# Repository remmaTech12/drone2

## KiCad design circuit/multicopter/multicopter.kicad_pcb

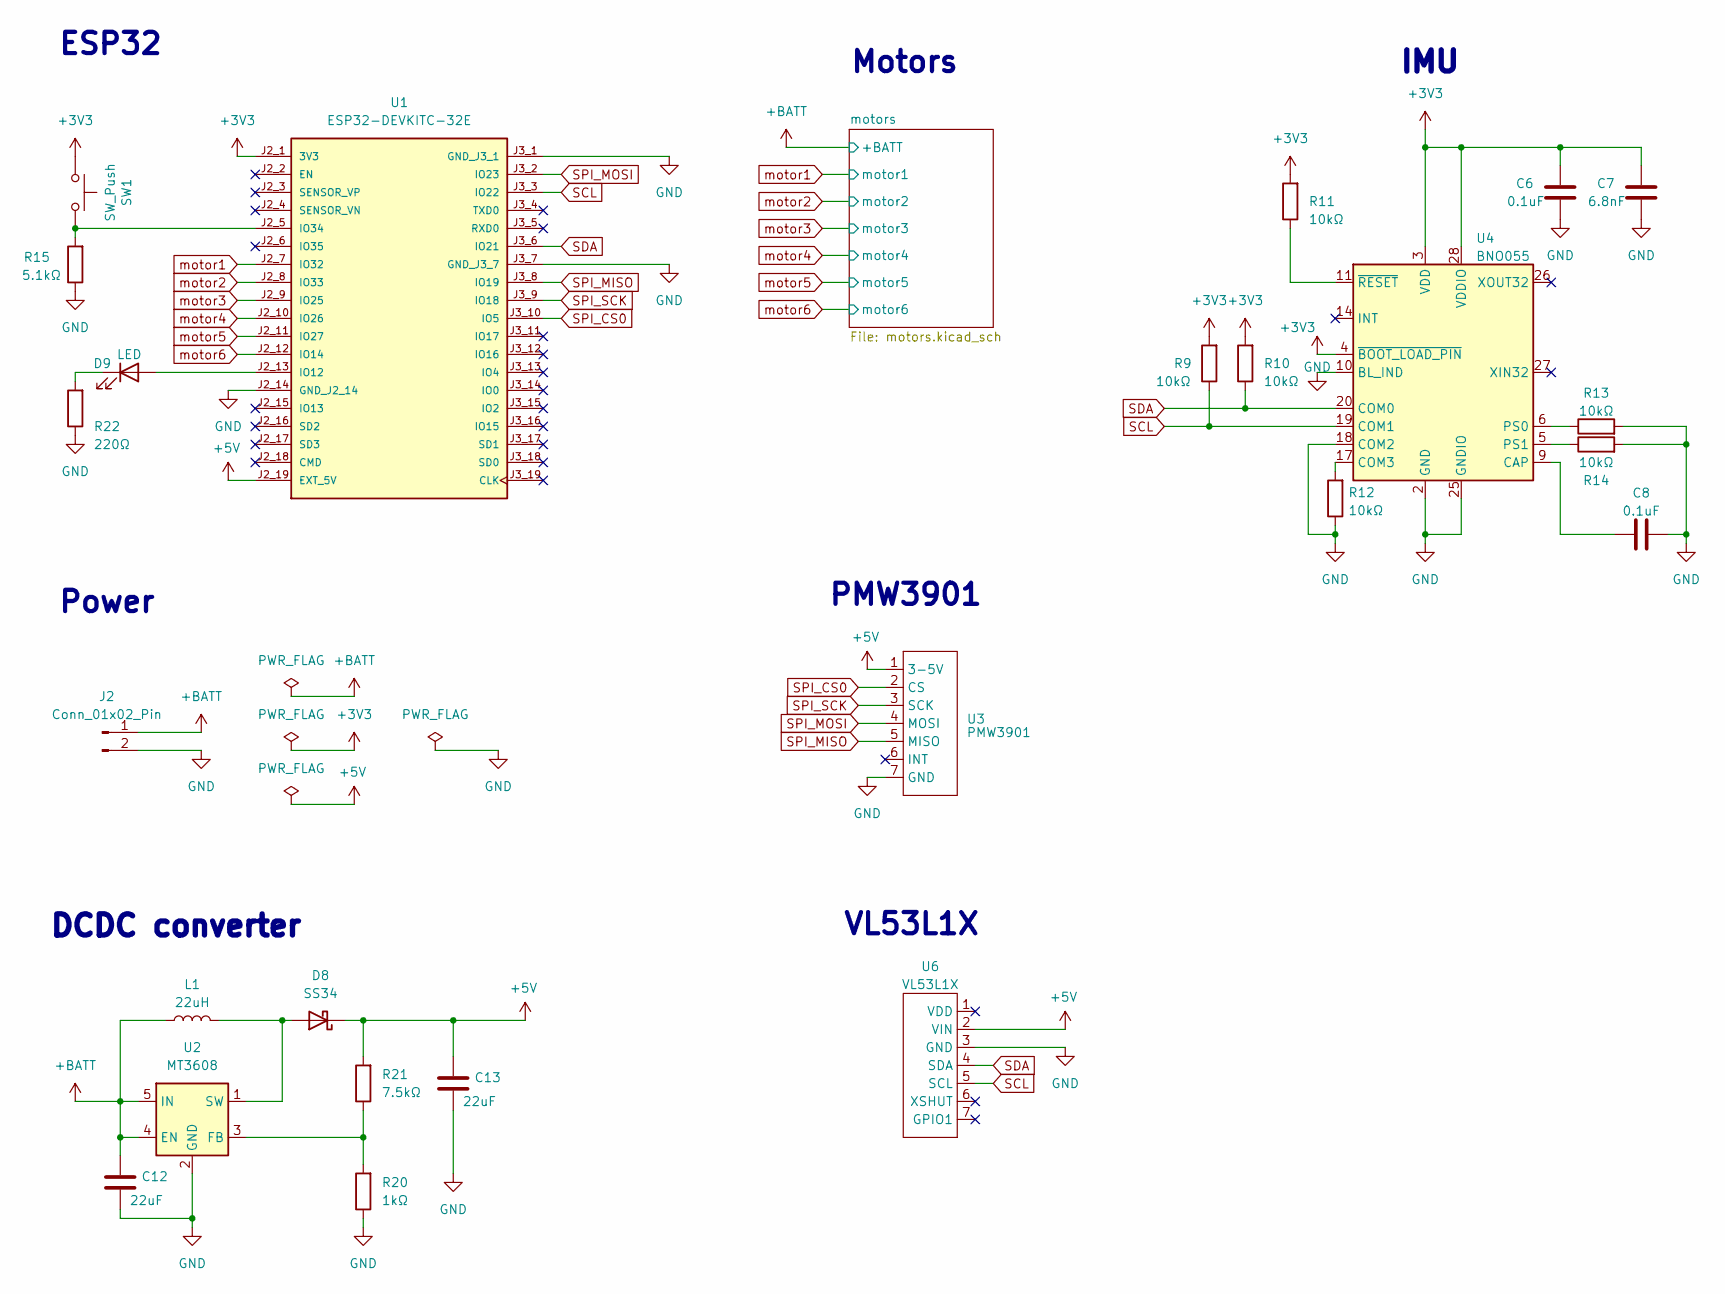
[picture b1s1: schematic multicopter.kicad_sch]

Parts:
C6, C8: 0.1uF; C_0603_1608Metric
C7: 6.8nF; C_0603_1608Metric
C12, C13: 22uF; C_0603_1608Metric
D8: SS34; D_SOD-123F
D9: LED; D_0603_1608Metric
J2: Conn_01x02_Pin; PinHeader_1x02_P2.54mm_Vertical
L1: 22uH; L_Vishay_IHLP-2020
R9, R10, R11, R12, R13, R14: 10kΩ; R_0603_1608Metric
R15: 5.1kΩ; R_0603_1608Metric
R20: 1kΩ; R_0603_1608Metric
R21: 7.5kΩ; R_0603_1608Metric
R22: 220Ω; R_0603_1608Metric
SW1: SW_Push; SW_Push_1P1T_NO_CK_KMR2
U1: ESP32-DEVKITC-32E; MODULE_ESP32-DEVKITC-32E; PARTREV 1.4
U2: MT3608; SOT-23-6
U3: PMW3901; JST_PH_B7B-PH-K_1x07_P2.00mm_Vertical
U4: BNO055; LGA-28_5.2x3.8mm_P0.5mm
U6: VL53L1X; JST_PH_B7B-PH-K_1x07_P2.00mm_Vertical

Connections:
+3V3: C6.2, C7.2, R9.2, R10.2, R11.2, SW1.1, U1.J2_1 (3V3), U4.3 (VDD), U4.4 (~BOOT_LOAD_PIN), U4.28 (VDDIO)
+5V: C13.1, D8.1 (K), R21.2, U1.J2_19 (EXT_5V), U3.1 (3-5V), U6.2 (VIN)
+BATT: C12.1, J2.1, L1.1, U2.4 (EN), U2.5 (IN); also elsewhere on the board
GND: C6.1, C7.1, C8.2, C12.2, C13.2, J2.2, R12.1, R13.2, R14.2, R15.1, R20.1, R22.1, U1.J2_14 (GND_J2_14), U1.J3_1 (GND_J3_1), U1.J3_7 (GND_J3_7), U2.2 (GND), U3.7 (GND), U4.2 (GND), U4.10 (BL_IND), U4.18 (COM2), U4.25 (GNDIO), U6.3 (GND); also elsewhere on the board
unnamed: D8.2 (A), L1.2, U2.1 (SW)
unnamed: D9.2 (A), U1.J2_13 (IO12)
unnamed: D9.1 (K), R22.2
unnamed: R15.2, SW1.2, U1.J2_5 (IO34)
unnamed: R20.2, R21.1, U2.3 (FB)
unnamed: C8.1, U4.9 (CAP)
unnamed: R12.2, U4.17 (COM3)
unnamed: R13.1, U4.6 (PS0)
unnamed: R14.1, U4.5 (PS1)
unnamed: R11.1, U4.11 (~RESET)
SCL: R9.1, U1.J3_3 (IO22), U4.19 (COM1), U6.5 (SCL)
SDA: R10.1, U1.J3_6 (IO21), U4.20 (COM0), U6.4 (SDA)
SPI_CS0: U1.J3_10 (IO5), U3.2 (CS)
SPI_MISO: U1.J3_8 (IO19), U3.5 (MISO)
SPI_MOSI: U1.J3_2 (IO23), U3.4 (MOSI)
SPI_SCK: U1.J3_9 (IO18), U3.3 (SCK)
motor1: U1.J2_7 (IO32); also elsewhere on the board
motor2: U1.J2_8 (IO33); also elsewhere on the board
motor3: U1.J2_9 (IO25); also elsewhere on the board
motor4: U1.J2_10 (IO26); also elsewhere on the board
motor5: U1.J2_11 (IO27); also elsewhere on the board
motor6: U1.J2_12 (IO14); also elsewhere on the board

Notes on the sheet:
Motors
VL53L1X
DCDC converter
PMW3901
Power
ESP32
IMU

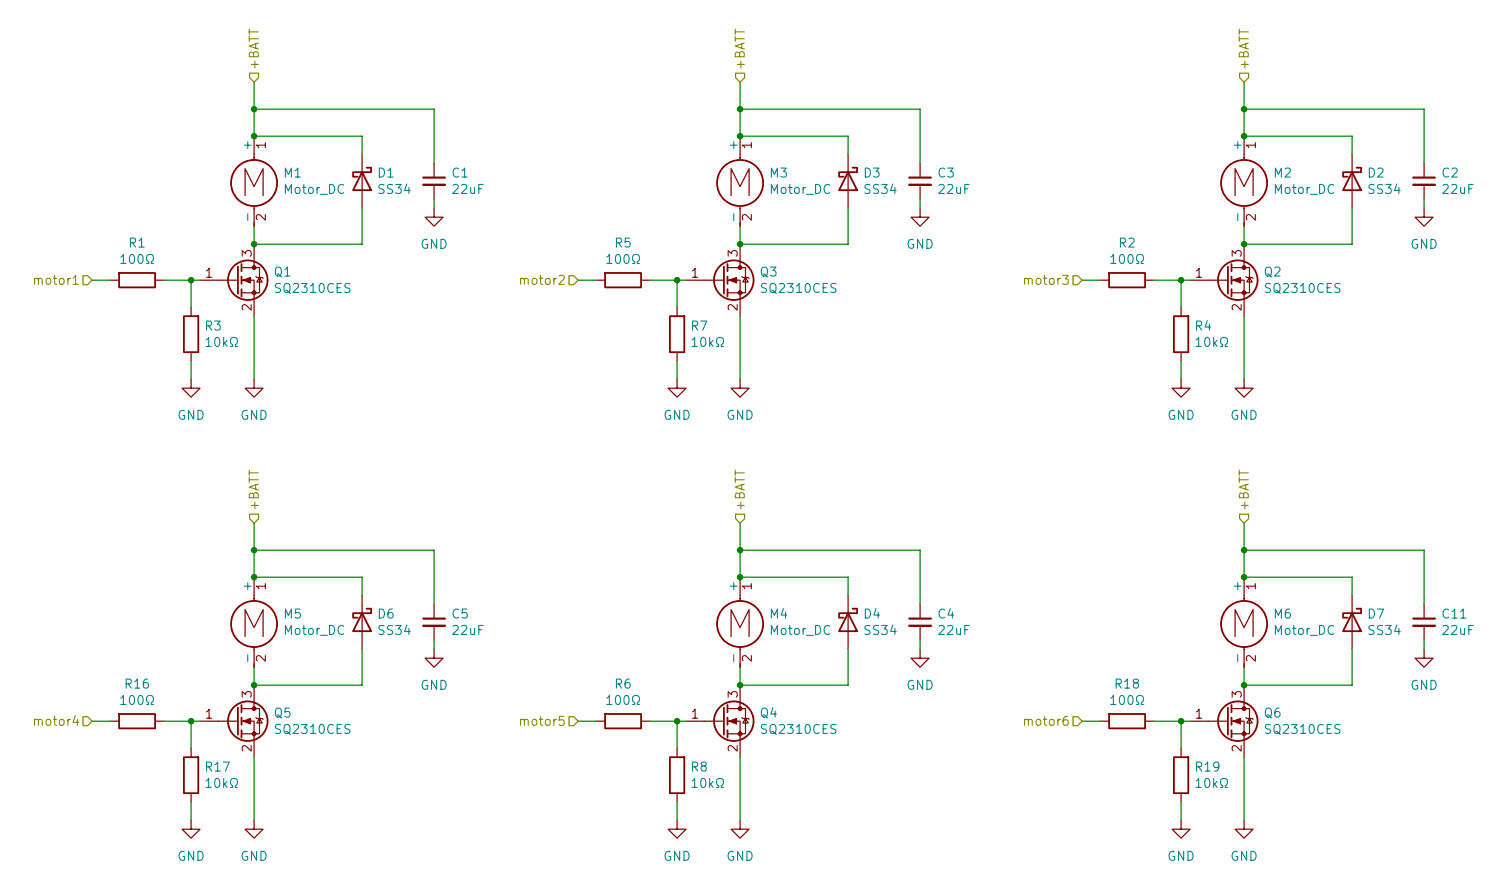
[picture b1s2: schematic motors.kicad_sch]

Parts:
C1, C2, C3, C4, C5, C11: 22uF; C_1206_3216Metric
D1, D2, D3, D4, D6, D7: SS34; D_SMC
M1, M2, M3, M4, M5, M6: Motor_DC; PinHeader_1x02_P2.54mm_Vertical
Q1, Q2, Q3, Q4, Q5, Q6: SQ2310CES; SOT-23
R1, R2, R5, R6, R16, R18: 100Ω; R_1210_3225Metric
R3, R4, R7, R8, R17, R19: 10kΩ; R_0201_0603Metric

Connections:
+BATT: C1.1, C2.1, C3.1, C4.1, C5.1, C11.1, D1.1 (K), D2.1 (K), D3.1 (K), D4.1 (K), D6.1 (K), D7.1 (K), M1.1 (+), M2.1 (+), M3.1 (+), M4.1 (+), M5.1 (+), M6.1 (+); also elsewhere on the board
GND: C1.2, C2.2, C3.2, C4.2, C5.2, C11.2, Q1.2 (S), Q2.2 (S), Q3.2 (S), Q4.2 (S), Q5.2 (S), Q6.2 (S), R3.1, R4.1, R7.1, R8.1, R17.1, R19.1; also elsewhere on the board
unnamed: D1.2 (A), M1.2 (-), Q1.3 (D)
unnamed: D2.2 (A), M2.2 (-), Q2.3 (D)
unnamed: D3.2 (A), M3.2 (-), Q3.3 (D)
unnamed: D4.2 (A), M4.2 (-), Q4.3 (D)
unnamed: D6.2 (A), M5.2 (-), Q5.3 (D)
unnamed: D7.2 (A), M6.2 (-), Q6.3 (D)
unnamed: Q1.1 (G), R1.1, R3.2
unnamed: Q2.1 (G), R2.1, R4.2
unnamed: Q3.1 (G), R5.1, R7.2
unnamed: Q4.1 (G), R6.1, R8.2
unnamed: Q5.1 (G), R16.1, R17.2
unnamed: Q6.1 (G), R18.1, R19.2
motor1: R1.2; also elsewhere on the board
motor2: R5.2; also elsewhere on the board
motor3: R2.2; also elsewhere on the board
motor4: R16.2; also elsewhere on the board
motor5: R6.2; also elsewhere on the board
motor6: R18.2; also elsewhere on the board

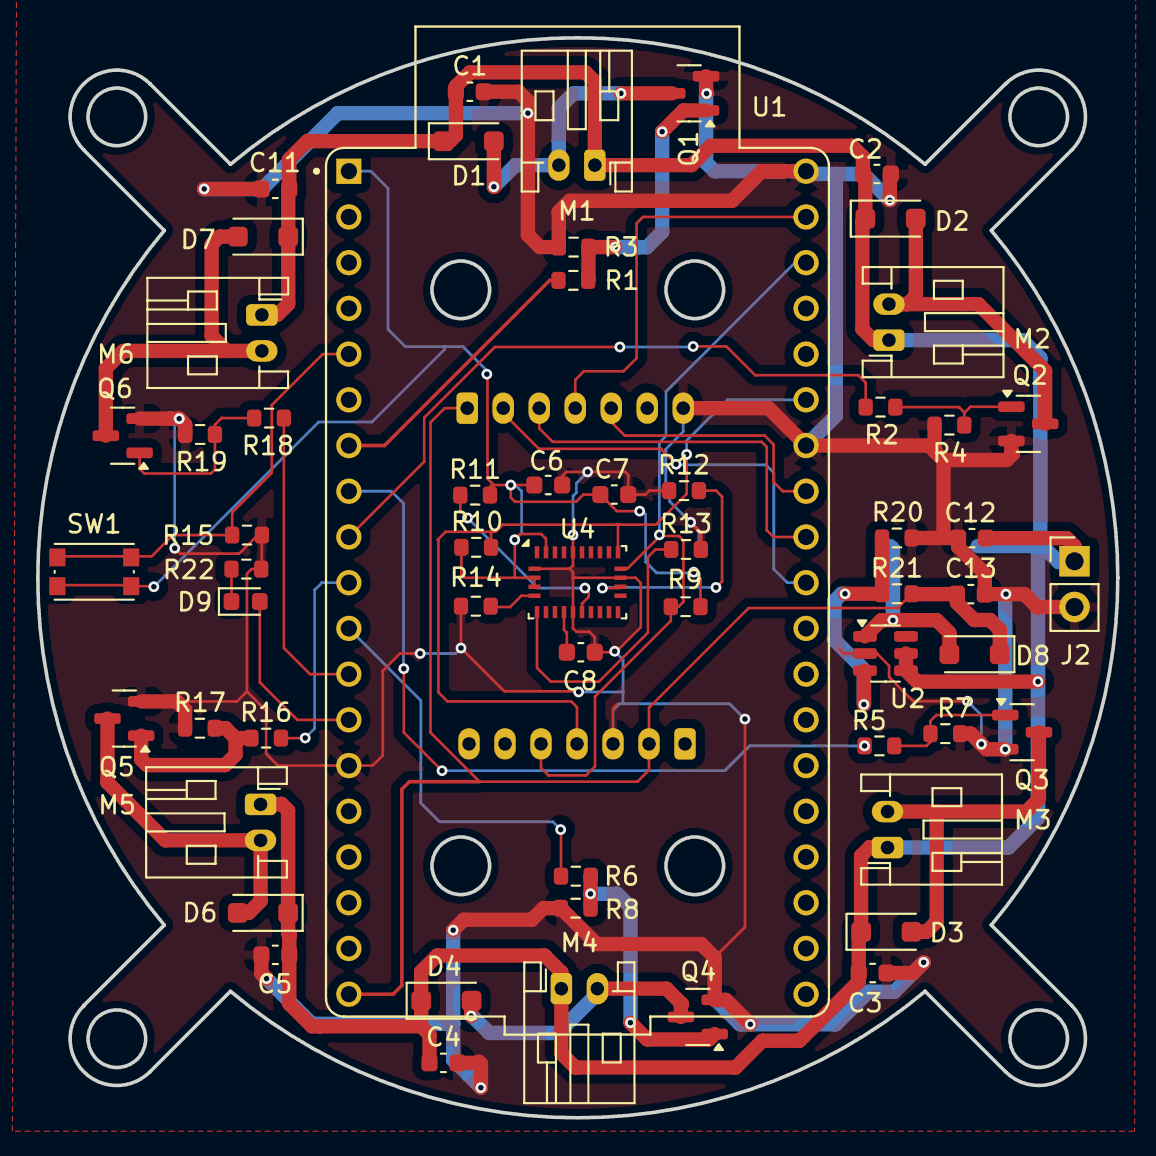
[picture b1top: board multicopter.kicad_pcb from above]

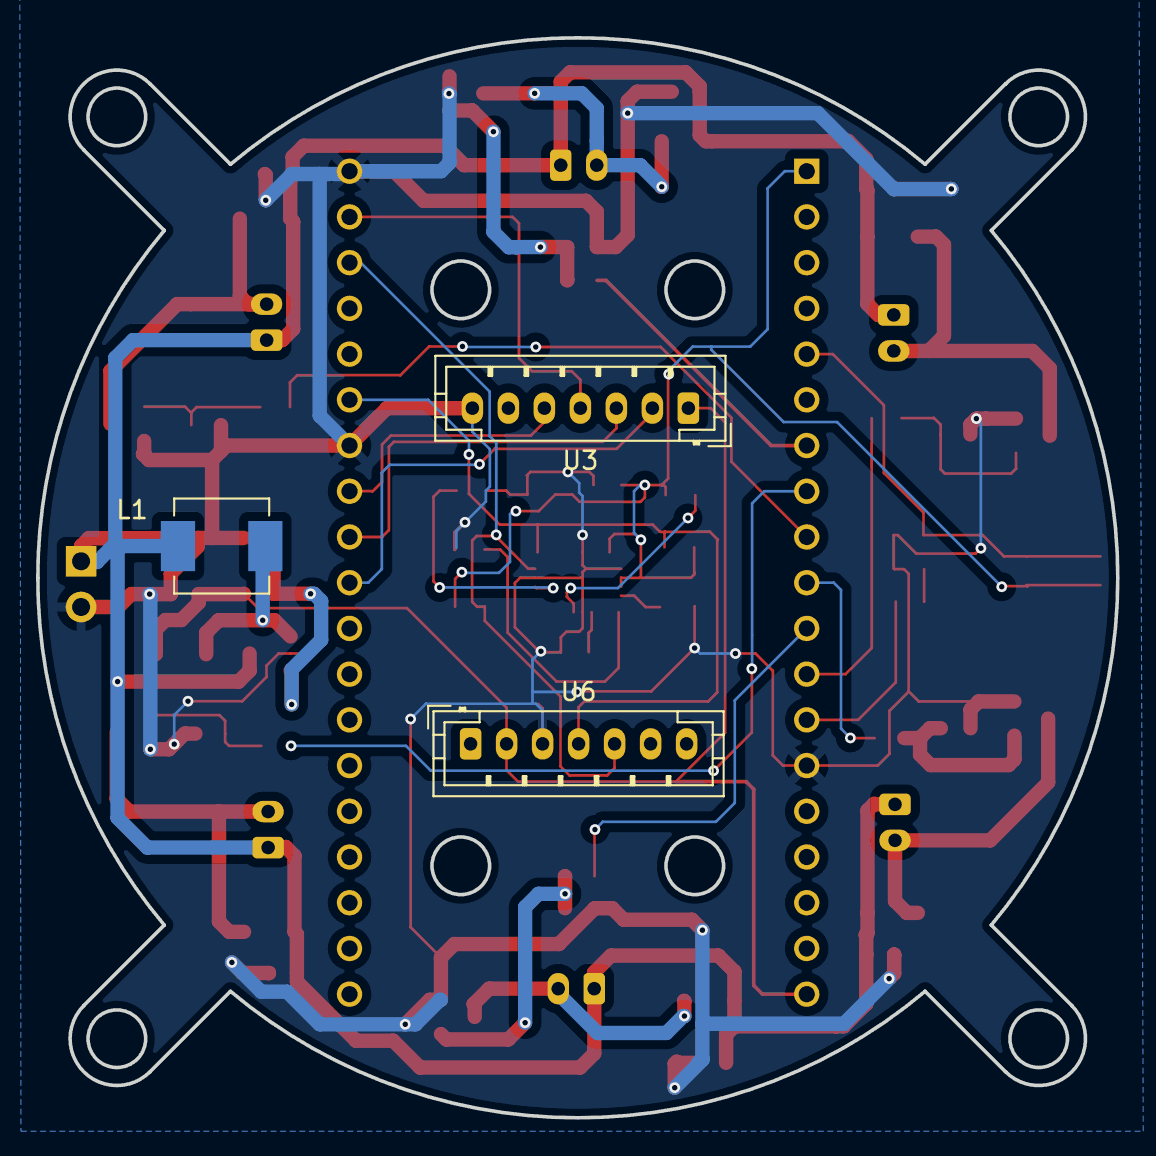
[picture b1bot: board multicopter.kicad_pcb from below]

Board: 2 copper layers, 60.0 x 60.0 mm, 61 parts (3 on the bottom side), 38 nets.

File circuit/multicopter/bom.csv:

"Designator","Description/Value","Package/Footprint","Quantity","Manufacturer","Purchase Link","Production Number","Mounting Type","Unit Price"
"J2","Conn_01x02_Pin","Connector_PinHeader_2.54mm:PinHeader_1x02_P2.54mm_Vertical","1","","","","THT",""
"U1","ESP32-DEVKITC-32E","ESP32-DEVKITC-32E:MODULE_ESP32-DEVKITC-32E","1","CXH","https://www.alibaba.com/product-detail/2-54mm-Pitch-1x19-pin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","","THT","74.66"
"R15","5.1kΩ","Resistor_SMD:R_0603_1608Metric","1","Vishay / Dale ","https://www.mouser.jp/ProductDetail/Vishay-Dale/CRCW06035K10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"," CRCW06035K10FKEC ","SMD","19.8"
"R20","1kΩ","Resistor_SMD:R_0603_1608Metric","1"," TDK ","https://www.mouser.jp/ProductDetail/TDK/MMZ1608S102ATA00?qs=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"," MMZ1608S102ATA00 ","SMD","16.5"
"M1,M2,M3,M4,M5,M6","Motor_DC","Connector_JST:JST_PH_S2B-PH-K_1x02_P2.00mm_Horizontal","6","JST Sales America Inc.","https://www.digikey.jp/en/products/detail/jst-sales-america-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"," S2B-PH-K-S","THT","15.04"
"C7","6.8nF","Capacitor_SMD:C_0603_1608Metric","1","Vishay / Vitramon ","https://www.mouser.jp/ProductDetail/Vishay-Vitramon/VJ0603Y6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"," VJ0603Y682KXBAC31X ","SMD","41.3"
"C1,C2,C3,C4,C5,C11,C12,C13","22uF","Capacitor_SMD:C_0603_1608Metric","8","KYOCERA AVX ","https://www.mouser.jp/ProductDetail/KYOCERA-AVX/0603ZD226MAT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","0603ZD226MAT2A ","SMD","85.8"
"U3","PMW3901","Connector_JST:JST_PH_B7B-PH-K_1x07_P2.00mm_Vertical","1","JST Sales America Inc.","https://www.digikey.jp/ja/products/detail/jst-sales-america-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","B7B-PH-K-S","THT","50.77"
"U6","VL53L1X","Connector_JST:JST_PH_B7B-PH-K_1x07_P2.00mm_Vertical","1","JST Sales America Inc.","https://www.digikey.jp/ja/products/detail/jst-sales-america-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","B7B-PH-K-S","THT","50.77"
"U4","BNO055","Package_LGA:LGA-28_5.2x3.8mm_P0.5mm","1","Bosch Sensortec","https://www.mouser.jp/ProductDetail/Bosch-Sensortec/BNO055?q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","BNO055","SMD","2,036.1 "
"R1,R2,R5,R6,R16,R18","100Ω","Resistor_SMD:R_0603_1608Metric","6","Bourns ","https://www.mouser.jp/ProductDetail/Bourns/CR0603-JW-101ELF?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","CR0603-JW-101ELF ","SMD","16.5"
"R22","220Ω","Resistor_SMD:R_0603_1608Metric","1","Pulse Electronics ","https://www.mouser.jp/ProductDetail/Pulse-Electronics/GBK160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","GBK160808T-221Y-N ","SMD","16.5"
"L1","22uH","Inductor_SMD:L_Vishay_IHLP-2020","1","Vishay / Dale ","https://www.mouser.jp/ProductDetail/Vishay-Dale/IHLP2020BZER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","IHLP2020BZER220M5A ","SMD","207.9"
"C6,C8","0.1uF","Capacitor_SMD:C_0603_1608Metric","2","KYOCERA AVX ","https://www.mouser.jp/ProductDetail/KYOCERA-AVX/KAM15AR71C10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","KAM15AR71C104KM ","SMD","56.1"
"SW1","SW_Push","Button_Switch_SMD:SW_Push_1P1T_NO_CK_KMR2","1","C&K","https://www.mouser.jp/ProductDetail/CK/KMR231NGLFS?qs=sb%252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","KMR231NGLFS","SMD","137"
"R3,R4,R7,R8,R9,R10,R11,R12,R13,R14,R17,R19","10kΩ","Resistor_SMD:R_0603_1608Metric","12","Vishay / Beyschlag ","https://www.mouser.jp/ProductDetail/Vishay-Beyschlag/MCT0603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","MCT06030D1002BP500 ","SMD","23.1"
"U2","MT3608","Package_TO_SOT_SMD:SOT-23-6","1","CYLDCHIP","https://ja.aliexpress.com/item/1005005498022711.html?src=goo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","MT3608","SMD","53"
"R21","7.5kΩ","Resistor_SMD:R_0603_1608Metric","1"," Susumu ","https://www.mouser.jp/ProductDetail/Susumu/RG1608P-752-B-T5?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","RG1608P-752-B-T5 ","SMD","34.7"
"D9","LED","Diode_SMD:D_0603_1608Metric","1","Bivar ","https://www.mouser.jp/ProductDetail/Bivar/SM0603UBWC?qs=hWDd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","SM0603UBWC ","SMD","242.6"
"Q1,Q2,Q3,Q4,Q5,Q6","SQ2310CES","Package_TO_SOT_SMD:SOT-23","6","Vishay / Siliconix ","https://www.mouser.jp/ProductDetail/Vishay-Siliconix/SQ2310C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","SQ2310CES-T1_GE3 ","SMD","77.6 "
"D1,D2,D3,D4,D6,D7,D8","SS34","Diode_SMD:D_SOD-123F","7"," onsemi / Fairchild ","https://www.mouser.jp/ProductDetail/onsemi-Fairchild/SS34FA?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","SS34FA ","SMD","62.7"

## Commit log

2025-02-15 initial commit: rotate one motor.
2025-02-18 rotate 6 motors.
2025-02-18 add pmw3901
2025-03-02 use motor pwm variable.
2025-03-02 add vl53l1x ToF sensor.
2025-03-09 Refactoring
2025-03-09 add multicopter breadboard circuit
2025-03-09 change directory name and structure.
2025-03-16 completed schematic.
2025-07-03 added circuits.
2025-07-03 add 3d prints.
2025-09-19 add 3d print parts.
2025-09-20 Removed unnecessary file.
2025-09-20 Utilize the previous drone code.
2025-09-21 build successful
2025-09-21 Control within a certain control frequency.
2025-09-21 removed unnecessarry codes.
2025-09-21 set the correct pin number for motors.
2025-09-21 Refactor control.cpp code: use variable / appropriate sentence length.
2025-09-21 Refactor: use constexpr.
2025-09-24 tidy up 3d print components.
2025-09-24 Fixed motor number definition.
2025-09-24 button uses pull down actually.
2025-09-24 Utilize the current bluetooth mac address.
2025-09-24 succeeded in test motor control.
2025-09-25 rotate motor soon after connected to controller.
2025-09-26 temporary commit: use BLE instead of bluetooth classic.
2025-09-26 Revert "temporary commit: use BLE instead of bluetooth classic."
    This reverts commit a20dd4facde794c9bfc8b75720899871815be649.
2025-09-26 utilize bluetooth to receive commands.
2025-09-28 add optical flow sensor.
2025-09-28 add tof sensor.
2025-09-29 fixed an issue of receive data from transmitter (need to check data ready).
2025-10-04 separate led functions.
2025-10-04 revise the 3d print part cad files.
2025-10-04 removed unnecessary debug sentence.
2025-10-04 added madgwick filter and euler angle calculation.
2025-10-04 removed madgwick and refactor.
2025-10-04 added quartenion calculation.
2025-10-04 not use magnetic sensor of IMU.
2025-10-04 add coordinate transformation for optical flow sensor.
2025-10-04 removed unnecessary comment out.
2025-10-04 add led on/off code.
2025-10-04 turn on led when armed.
2025-10-05 add debug message flags.
2025-10-05 stay hover program.
2025-10-05 remove unnecessary space.
2025-10-05 use deg instead of rad.
2025-10-05 change the light brightness for on/off.
2025-10-05 fixed motor pin allocation.
2025-10-05 update 3d print parts.
2025-10-05 add getter function for tof sensor.
2025-10-05 revert temporarly code.
2025-10-05 call control with height.
2025-10-05 added an algorithm of thrust calculation based on height.
2025-10-05 add i control for thrust based on height.
2025-10-06 suppress electrical consumption by releasing ble memory.
2025-10-06 utilize optical flow data for attitude control.
2025-10-06 add calibration.
2025-10-06 add 3dprint data.
2025-10-07 separate control frequency for outer and inner and remove pid.h/pid.cpp.
2025-10-07 bug fix for neutral command.
2025-10-08 tune PID gain.
2025-10-08 tune the maximum integral term and low pass filter parameter.
2025-10-08 add offset for roll and pitch angles.
2025-10-08 remove offsets for motors and use previous thrust calculation algorithm.
2025-10-08 add moving average to eliminate noise.
2025-10-08 add library for low pass filter and moving average.
2025-10-08 calculate position deviation and velocity.
2025-10-08 get float data for flow sensor.
2025-10-08 add position control with flow sensor.
2025-10-08 add disarm function for over-rotation.
2025-10-09 relatively working well gain control.h
2025-10-09 a bit more stable gain.
2025-10-09 add debug feature flag
2025-10-09 add angle compensation
2025-10-09 add zero clear, debug sentence, and not use position control temporarily.
2025-10-09 remove bias and calibration, and add debug sentence for imu.
2025-10-09 separate control frequency for position control.
2025-10-09 working well gain and add maximum output value.
2025-10-09 quit integral of flow sensor.
2025-10-09 raise thrust scale.
2025-10-09 successful flight: decrease moving_average window size and limit angle.
2025-10-09 add offset for pitch angle.
2025-10-10 add low pass filter for motor commands.
2025-10-10 add tilt-cone limiter.
2025-10-10 remove offset.
2025-10-10 successful flight: shorten position control cycle.
2025-10-11 output detail log.
2025-10-11 successful flight 9s: add joystick command
2025-10-11 refactoring: formatting command.
2025-10-11 refactor d term calculation of position control.
2025-10-11 remove useless comments and codes on control.cpp
2025-10-11 remove integral term clear.
2025-10-11 check nan or inf for imu sensor.
2025-10-11 remove useless comments on recv.cpp.
2025-10-11 rename from hpp to h.
2025-10-11 remove unnecessary emergency files.
2025-10-11 use pragma once.
2025-10-11 separate xy command calculation.
2025-10-11 added debug message.
2025-10-11 add motor bracket 3dprint files.
2025-10-11 simplified pid calculation source code.
2025-10-11 Created a function to calculate PID.
2025-10-11 refactoring: function name.
2025-10-11 use new pid algorithm for attitude control.
2025-10-11 refactor: add a function to translate a command.
2025-10-11 finish refactoring of control component.
2025-10-11 finished refactoring of def_systems.h
2025-10-11 refactor flow sensor code.
2025-10-11 imu refactoring done.
2025-10-11 remove unnecessary variable.
2025-10-11 refactor for motor is done.
2025-10-11 refacor for flow sensor is done.
2025-10-11 refactor for receiver is done.
2025-10-18 bug fix for angle initialization.
2025-10-18 good performance without thrust scale.
